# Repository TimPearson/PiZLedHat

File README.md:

# PiZLedHat

## A hat - to drive LEDs from a Pi Zero part of the Platform Lighting Project
### Part of the Platform Lighting Project

This a PCB design in EAGLE CAD, it can be used to make a hat to sit on a PiZero and drive a batch of LEDS - It also has an interface and step down facility so the LEDs and the PiZero can be driven off the same 9V power supply.

Parts List:\
3 x ULN2003A-DIL NPN Seven Darlington Array\
1 x 40 PIN (2x20) 2.54mm pitch Female Header\
1 x TSR 1-2450 DC/DC converter\
1 x 2 Way PCB Terminal Block Connector 2.54mm pitch\
4 x IDC Box Header Connector 10 Way 2.54mm pitch\

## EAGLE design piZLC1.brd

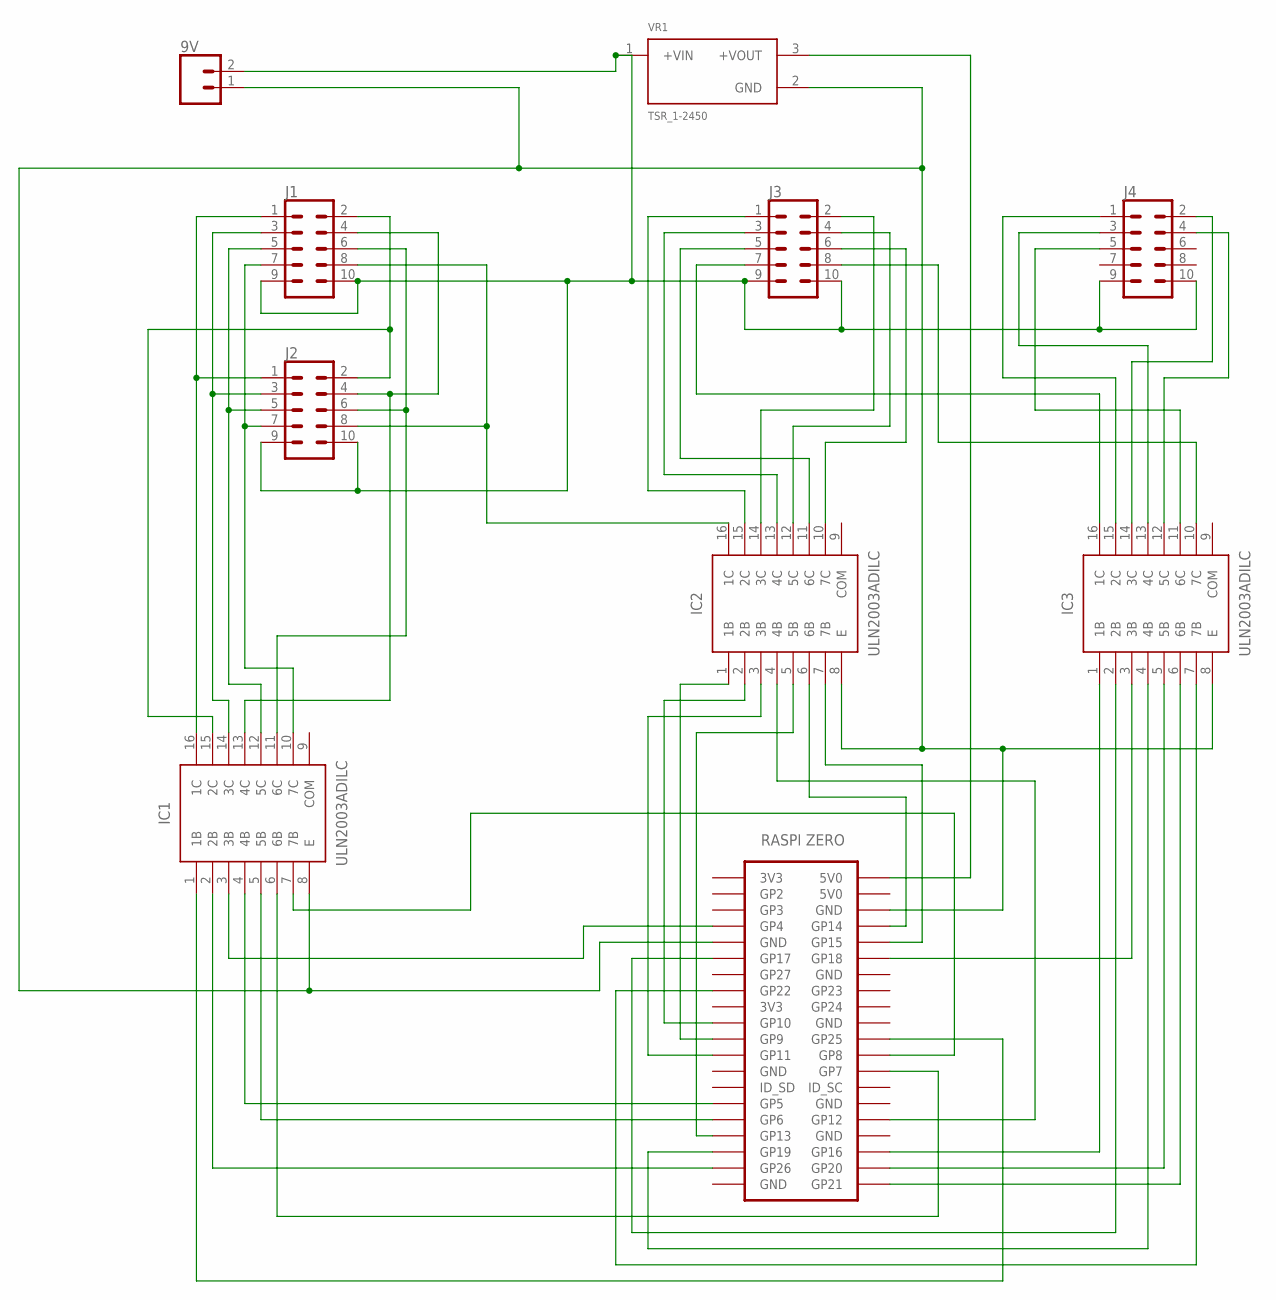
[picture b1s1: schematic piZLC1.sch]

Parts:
9V: CONN_023.5MM; SCREWTERMINAL-3.5MM-2
IC1, IC2, IC3: ULN2003ADILC; DIL16
J1, J2, J3, J4: CONN_05X2SHD; 2X5-SHROUDED
U$1: ZERO
VR1: TSR_1-2450; CONV_TSR_1-2450

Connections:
COM: IC1.9 (COM), IC2.9 (COM), IC3.9 (COM)
unnamed: U$1.4 (5V0), VR1.3 (+VOUT)
unnamed: IC1.16 (1C), J1.1, J2.1
unnamed: IC1.14 (3C), J1.3, J2.3
unnamed: IC1.12 (5C), J1.5, J2.5
unnamed: IC1.10 (7C), J1.7, J2.7
unnamed: IC1.1 (1B), U$1.22 (GP25)
unnamed: IC1.2 (2B), U$1.37 (GP26)
unnamed: IC1.3 (3B), U$1.7 (GP4)
unnamed: IC1.4 (4B), U$1.29 (GP5)
unnamed: IC1.5 (5B), U$1.31 (GP6)
unnamed: IC1.6 (6B), U$1.26 (GP7)
unnamed: IC1.7 (7B), U$1.24 (GP8)
unnamed: IC1.15 (2C), J1.2, J2.2
unnamed: 9V.1, IC1.8 (E), IC2.8 (E), IC3.8 (E), U$1.6 (GND), U$1.9 (GND), VR1.2 (GND)
unnamed: IC1.13 (4C), J1.4, J2.4
unnamed: IC1.11 (6C), J1.6, J2.6
unnamed: IC2.16 (1C), J1.8, J2.8
unnamed: IC2.1 (1B), U$1.21 (GP9)
unnamed: IC2.2 (2B), U$1.19 (GP10)
unnamed: IC2.3 (3B), U$1.23 (GP11)
unnamed: IC2.4 (4B), U$1.32 (GP12)
unnamed: IC2.5 (5B), U$1.33 (GP13)
unnamed: IC2.6 (6B), U$1.8 (GP14)
unnamed: IC2.7 (7B), U$1.10 (GP15)
unnamed: IC3.1 (1B), U$1.36 (GP16)
unnamed: IC3.2 (2B), U$1.11 (GP17)
unnamed: IC3.3 (3B), U$1.12 (GP18)
unnamed: IC3.4 (4B), U$1.35 (GP19)
unnamed: IC3.5 (5B), U$1.38 (GP20)
unnamed: IC3.6 (6B), U$1.40 (GP21)
unnamed: IC3.7 (7B), U$1.15 (GP22)
unnamed: IC2.15 (2C), J3.1
unnamed: IC2.14 (3C), J3.2
unnamed: IC2.13 (4C), J3.3
unnamed: IC2.12 (5C), J3.4
unnamed: IC2.11 (6C), J3.5
unnamed: IC2.10 (7C), J3.6
unnamed: IC3.16 (1C), J3.7
unnamed: IC3.15 (2C), J4.1
unnamed: IC3.14 (3C), J4.2
unnamed: IC3.13 (4C), J4.3
unnamed: IC3.12 (5C), J4.4
unnamed: IC3.11 (6C), J4.5
unnamed: IC3.10 (7C), J3.8
unnamed: 9V.2, J1.9, J1.10, J2.9, J2.10, J3.9, J3.10, J4.9, J4.10, VR1.1 (+VIN)

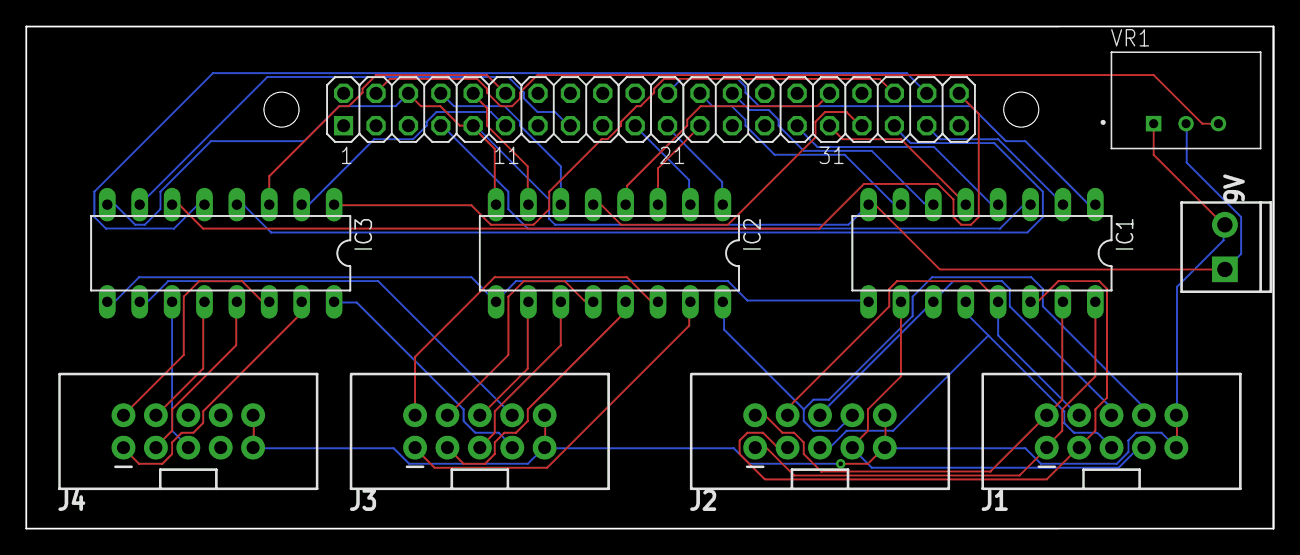
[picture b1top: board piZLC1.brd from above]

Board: 2 copper layers, 97.8 x 39.4 mm, 10 parts (0 on the bottom side), 46 nets.

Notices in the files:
parts and their libraries:
SparkFun-Connectors: Licensing: Creative Commons ShareAlike 4.0 International - https://creativecommons.org/licenses/by-sa/4.0
